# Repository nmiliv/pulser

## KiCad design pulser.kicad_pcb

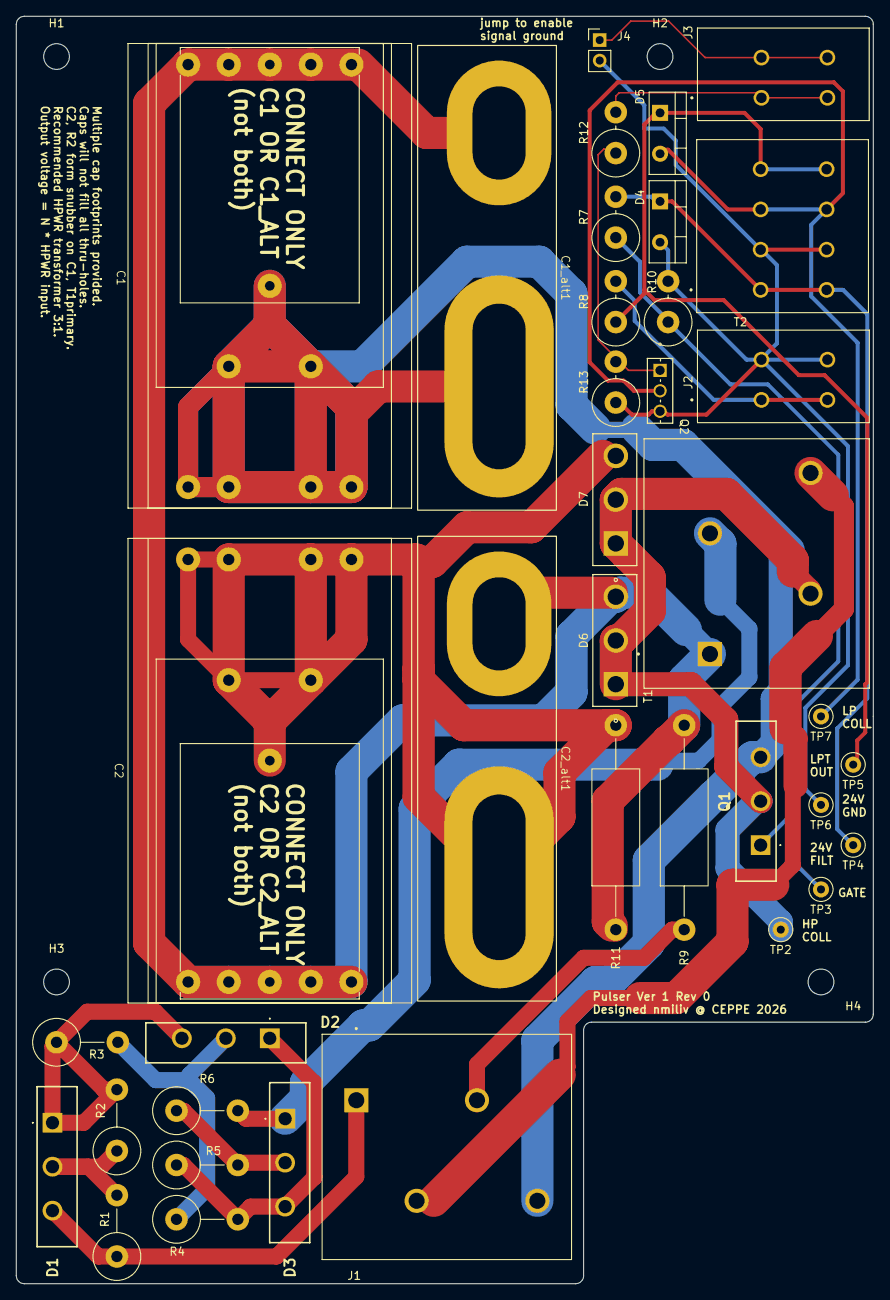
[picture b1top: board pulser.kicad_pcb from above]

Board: 2 copper layers, 106.5 x 157.5 mm, 42 parts (0 on the bottom side), 22 nets.

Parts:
C1: 1u; C_Rect_Kemet_Combined
C1_alt1, C2_alt1: 0; C_Slot_L22-41mm_M6_C4BS
C2: 3u; C_Rect_Kemet_Combined
D1, D2, D3: D_Dual_Series_ACK; DSEE30-12A
D4, D5: D; TO-220-2_Vertical
D6, D7: D_Dual_CommonCathode_AAK_Parallel; C4D40120D
H1, H2, H3, H4: MountingScrew; MountingHole_3.2mm_M3
J1: Conn_01x02_Pin; PHOENIX_1098177
J2: Conn_Coaxial_Power; PHOENIX_1190363
J3: Conn_Coaxial; PHOENIX_1190363
J4: Conn_01x02_Pin; PinHeader_1x02_P2.54mm_Vertical
Q1: IXGK100N170; IXBK75N170
Q2: Q_NPN; BD135_SOT-32_STM
R1, R2, R3, R4, R5, R6: 4k; R_Axial_DIN0614_L14.3mm_D5.7mm_P7.62mm_Vertical
R7, R8, R12: 100; R_Axial_DIN0614_L14.3mm_D5.7mm_P5.08mm_Vertical
R9: 220; R_Axial_DIN0614_L14.3mm_D5.7mm_P25.40mm_Horizontal
R10: 1k; R_Axial_DIN0614_L14.3mm_D5.7mm_P5.08mm_Vertical
R11: 110; R_Axial_DIN0614_L14.3mm_D5.7mm_P25.40mm_Horizontal
R13: 1Meg; R_Axial_DIN0614_L14.3mm_D5.7mm_P5.08mm_Vertical
T1: 1:3; PHOENIX_1098177
T2: 1:1; PHOENIX_1190365
TP2, TP3, TP4, TP5, TP6, TP7: TestPoint; TestPoint_Loop_D1.80mm_Drill1.0mm_Beaded

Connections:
+24V: J2.1_1, J2.1_2, R8.2
AC: J3.1_1, J3.1_2, R12.2
Earth: D4.2 (A), J2.2_1, J2.2_2, J4.2, Q2.E, R10.2, R13.1, T2.2 (AB), TP6.1 (1_1)
GND: C1.2, C1_alt1.2, J1.4, Q1.3 (E)
unnamed: D1.1 (A), D2.3 (K), R2.2, R3.1
unnamed: D1.3 (K), J1.1, R1.1
unnamed: D1.2 (common), R1.2, R2.1
unnamed: D2.1 (A), D3.3 (K), R4.2, R5.1
unnamed: D2.2 (common), R3.2, R4.1
unnamed: D3.1 (A), R6.2, T1.3 (SA)
unnamed: D3.2 (common), R5.2, R6.1
unnamed: D4.1 (K), R7.2, T2.1 (AA), TP4.1 (1_1)
unnamed: D5.2 (A), Q2.C, T2.3 (SA), TP7.1 (1_1)
unnamed: D5.1 (K), R8.1, T2.4 (SB), TP5.1 (1_1)
unnamed: C1.1, C1_alt1.1, C2.1, C2_alt1.1, D6.3 (K), R9.2, R11.1, T1.1 (AA)
unnamed: C2.2, C2_alt1.2, D7.3 (K), R11.2
unnamed: J3.2_1, J3.2_2, J4.1
unnamed: D6.1 (A), D6.2 (A), D7.1 (A), D7.2 (A), Q1.2 (C), T1.2 (AB), TP2.1 (1_1)
unnamed: Q1.1 (G), R7.1, R10.1, TP3.1 (1_1)
unnamed: Q2.B, R12.1, R13.2
unnamed: J1.2, T1.4 (SB)
Vdrive: J1.3, R9.1

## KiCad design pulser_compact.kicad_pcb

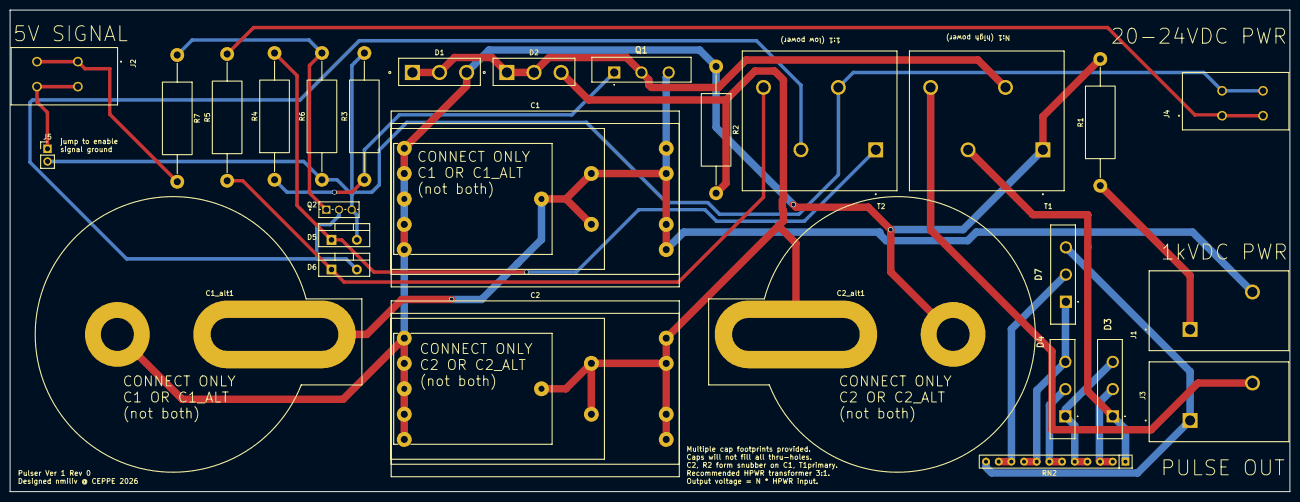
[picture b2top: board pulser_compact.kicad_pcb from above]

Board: 2 copper layers, 256.5 x 96.5 mm, 28 parts (0 on the bottom side), 22 nets.

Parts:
C1: 1u; C_Rect_Kemet_Combined
C1_alt1: 0; C_Slot_L22-41mm_M6
C2: 3u; C_Rect_Kemet_Combined
C2_alt1: 0; C_Slot_L22-41mm_M6_reverse
D1, D2: D_Dual_CommonCathode_AAK_Parallel; C4D40120D
D3, D4, D7: D_Dual_Series_ACK; DSEE30-12A
D5, D6: D; TO-220-2_Vertical
J1: Conn_Coaxial_Power; PHOENIX_1098175
J2: Conn_Coaxial; PHOENIX_1190363
J3: Conn_01x02_Pin; PHOENIX_1098175
J4: Conn_Coaxial_Power; PHOENIX_1190363
J5: Conn_01x02_Pin; PinHeader_1x02_P2.54mm_Vertical
Q1: IXBK75N170
Q2: Q_NPN; BD135_SOT-32_STM
R1: 220; R_Axial_DIN0614_L14.3mm_D5.7mm_P25.40mm_Horizontal
R2: 110; R_Axial_DIN0614_L14.3mm_D5.7mm_P25.40mm_Horizontal
R3: 1k; R_Axial_DIN0614_L14.3mm_D5.7mm_P25.40mm_Horizontal
R4, R5, R6, R7: R; R_Axial_DIN0614_L14.3mm_D5.7mm_P25.40mm_Horizontal
RN2: 4k; R_Array_SIP12
T1: 1:3; PHOENIX_1098177
T2: 1:1; PHOENIX_1098177

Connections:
+24V: J4.1_1, J4.1_2, R5.2
AC: J2.1_1, J2.1_2, R7.2
Earth: D5.2 (A), J4.2_1, J4.2_2, J5.2, Q2.E, R3.2, R6.1, T2.2 (AB)
GND: C1.2, C1_alt1.2, J1.2 (Ext), Q1.3 (E)
unnamed: C1.1, C1_alt1.1, C2.1, C2_alt1.1, D1.3 (K), R1.2, R2.1, T1.1 (AA)
unnamed: C2.2, C2_alt1.2, D2.3 (K), R2.2
unnamed: D3.1 (A), RN2.1 (R1.1), T1.3 (SA)
unnamed: D3.3 (K), D4.1 (A), RN2.4 (R2.2), RN2.5 (R3.1)
unnamed: D3.2 (common), RN2.2 (R1.2), RN2.3 (R2.1)
unnamed: D4.3 (K), D7.1 (A), RN2.8 (R4.2), RN2.9 (R5.1)
unnamed: D4.2 (common), RN2.6 (R3.2), RN2.7 (R4.1)
unnamed: D5.1 (K), R4.2, T2.1 (AA)
unnamed: D6.2 (A), Q2.C, T2.3 (SA)
unnamed: D6.1 (K), R5.1, T2.4 (SB)
unnamed: D7.3 (K), J3.1, RN2.12 (R6.2)
unnamed: D7.2 (common), RN2.10 (R5.2), RN2.11 (R6.1)
unnamed: J3.2, T1.4 (SB)
unnamed: J2.2_1, J2.2_2, J5.1
unnamed: D1.1 (A), D1.2 (A), D2.1 (A), D2.2 (A), Q1.2 (C), T1.2 (AB)
unnamed: Q1.1 (G), R3.1, R4.1
unnamed: Q2.B, R6.2, R7.1
Vdrive: J1.1 (In), R1.1
